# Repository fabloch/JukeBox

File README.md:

# Jukebox
Juke-Box avec une puce RFID

> Définition de Jukebox : Électrophone automatique, généralement payant, que l’on retrouve dans certains lieux publics et qui permet de faire jouer un disque sélectionné. (Définition d’Antidote)

> Définition de RFID : Sigle de Radio frequency identification.

Le Jukebox électriquement est composé de 3 parties : 
1. Une partie qui est en charge de la puce RFID 
2. La seconde partie quant à elle est chargée de la partie lecture du fichier MP3 et de l’amplification audio.
3. Le tout est supervisé par une carte Arduino UNO

## Liste des composant

- PUCE RFID
- Carte Arduino Uno 
- Boutons poussoir 
- Connecteur Jack 
- Amplificateur et lecteur de carte SD
- Potentiomètre 
	 
## Le code es quand à lui es écrit en Arduino 

Ici c’es le code de la partie du player du jukebox

```c
/*
   Thanks to Original Author: ryand1011 (https://github.com/ryand1011)
   Edited by Ananords -

   See: https://github.com/miguelbalboa/rfid/tree/master/examples/rfid_write_personal_data

   Uses MIFARE RFID card using RFID-RC522 reader
   Uses MFRC522 - Library
   -----------------------------------------------------------------------------------------
               MFRC522      Arduino       Arduino   Arduino    Arduino          Arduino
               Reader/PCD   Uno/101       Mega      Nano v3    Leonardo/Micro   Pro Micro
   Signal      Pin          Pin           Pin       Pin        Pin              Pin
   -----------------------------------------------------------------------------------------
   RST/Reset   RST          9             5         D9         RESET/ICSP-5     RST
   SPI SS      SDA(SS)      10            53        D10        10               10
   SPI MOSI    MOSI         11 / ICSP-4   51        D11        ICSP-4           16
   SPI MISO    MISO         12 / ICSP-1   50        D12        ICSP-1           14
   SPI SCK     SCK          13 / ICSP-3   52        D13        ICSP-3           15

  PS: IF THE PLAYER FAILS TO START WHEN THE SERIAL MONITOR IS NOT OPEN, TRY TO COMMENT OUT Serial.begin(115200);
*/

#include <SPI.h>
#include <MFRC522.h>
#include "Arduino.h"
#include "SoftwareSerial.h"
#include "DFRobotDFPlayerMini.h"

#define RST_PIN         9           // Configurable, see typical pin layout above
#define SS_PIN          10          // Configurable, see typical pin layout above

const int playPauseButton = 4;
const int shuffleButton = 3;
const byte volumePot = A0;
int prevVolume; 

byte volumeLevel = 0; //variable for holding volume level

boolean isPlaying = false;

MFRC522 mfrc522(SS_PIN, RST_PIN);   // Create MFRC522 instance

SoftwareSerial mySoftwareSerial(5, 6); // RX, TX

DFRobotDFPlayerMini myDFPlayer;
void printDetail(uint8_t type, int value);

//*****************************************************************************************//
void setup() {
  Serial.begin(115200);                                           // Initialize serial communications with the PC, COMMENT OUT IF IT FAILS TO PLAY WHEN DISCONNECTED FROM PC
  mySoftwareSerial.begin(9600);
  SPI.begin();                                                  // Init SPI bus
  mfrc522.PCD_Init();                                              // Init MFRC522 card

  pinMode(playPauseButton, INPUT_PULLUP);
  pinMode(shuffleButton, INPUT_PULLUP);

  Serial.println(F("Initializing DFPlayer ... (May take 3~5 seconds)"));

  if (!myDFPlayer.begin(mySoftwareSerial)) {  //Use softwareSerial to communicate with mp3.
    Serial.println(F("Unable to begin:"));
    Serial.println(F("1.Please recheck the connection!"));
    Serial.println(F("2.Please insert the SD card!"));
  }
  Serial.println(F("DFPlayer Mini online. Place card on reader to play a spesific song"));

  //myDFPlayer.volume(15);  //Set volume value. From 0 to 30 
  volumeLevel = map(analogRead(volumePot), 0, 1023, 0, 30);   //scale the pot value and volume level
  myDFPlayer.volume(volumeLevel);
  prevVolume = volumeLevel;

  //----Set different EQ----
  myDFPlayer.EQ(DFPLAYER_EQ_NORMAL);
  //  myDFPlayer.EQ(DFPLAYER_EQ_POP);
  //  myDFPlayer.EQ(DFPLAYER_EQ_ROCK);
  //  myDFPlayer.EQ(DFPLAYER_EQ_JAZZ);
  //  myDFPlayer.EQ(DFPLAYER_EQ_CLASSIC);
  //  myDFPlayer.EQ(DFPLAYER_EQ_BASS);

}

//*****************************************************************************************//
void loop() {

  volumeLevel = map(analogRead(volumePot), 0, 1023, 0, 30);   //scale the pot value and volume level

  if (prevVolume != volumeLevel){
  myDFPlayer.volume(volumeLevel);
  }
    prevVolume = volumeLevel;

  // Prepare key - all keys are set to FFFFFFFFFFFFh at chip delivery from the factory.
  MFRC522::MIFARE_Key key;
  for (byte i = 0; i < 6; i++) key.keyByte[i] = 0xFF;

  //some variables we need
  byte block;
  byte len;
  MFRC522::StatusCode status;

  if (digitalRead(playPauseButton) == LOW) {
    if (isPlaying) {
      myDFPlayer.pause();
      isPlaying = false;
      Serial.println("Paused..");
    }
    else {
      isPlaying = true;
      myDFPlayer.start();
      Serial.println("Playing..");
    }
    delay(500);
  }

  if (digitalRead(shuffleButton) == LOW) {
    myDFPlayer.randomAll();
    Serial.println("Shuffle Play");
    isPlaying = true;
    delay(1000);
  }

  //-------------------------------------------

  // Reset the loop if no new card present on the sensor/reader. This saves the entire process when idle.
  if ( mfrc522.PICC_IsNewCardPresent()) {

    // Select one of the cards
    if ( ! mfrc522.PICC_ReadCardSerial()) {
      return;
    }

    Serial.println(F("**Card Detected:**"));

    //-------------------------------------------

    mfrc522.PICC_DumpDetailsToSerial(&(mfrc522.uid)); //dump some details about the card

    //mfrc522.PICC_DumpToSerial(&(mfrc522.uid));      //uncomment this to see all blocks in hex

    //-------------------------------------------

    Serial.print(F("Number: "));

    //---------------------------------------- GET NUMBER AND PLAY THE SONG

    byte buffer2[18];
    block = 1;
    len = 18;

    status = mfrc522.PCD_Authenticate(MFRC522::PICC_CMD_MF_AUTH_KEY_A, 1, &key, &(mfrc522.uid)); //line 834
    if (status != MFRC522::STATUS_OK) {
      Serial.print(F("Authentication failed: "));
      Serial.println(mfrc522.GetStatusCodeName(status));
      return;
    }

    status = mfrc522.MIFARE_Read(block, buffer2, &len);
    if (status != MFRC522::STATUS_OK) {
      Serial.print(F("Reading failed: "));
      Serial.println(mfrc522.GetStatusCodeName(status));
      return;
    }

    //PRINT NUMBER
    String number = "";

    for (uint8_t i = 0; i < 16; i++)
    {
      number += (char)buffer2[i];
    }
    number.trim();
    Serial.print(number);

    //PLAY SONG

    myDFPlayer.play(number.toInt());
    isPlaying = true;

    //----------------------------------------

    Serial.println(F("\n**End Reading**\n"));

    delay(1000); //change value if you want to read cards faster

    mfrc522.PICC_HaltA();
    mfrc522.PCD_StopCrypto1();
  }
}

//*****************************************************************************************//

```

Juke Card programmer

Ici c’es le code source qui sert pour le programmer la jukebox. 

```c
/*
   Write song number data to a MIFARE RFID card using a RFID-RC522 reader
   Uses MFRC522 - Library to use ARDUINO RFID MODULE KIT 13.56 MHZ WITH TAGS SPI W AND R BY COOQROBOT.
   -----------------------------------------------------------------------------------------
               MFRC522      Arduino       Arduino   Arduino    Arduino          Arduino
               Reader/PCD   Uno/101       Mega      Nano v3    Leonardo/Micro   Pro Micro
   Signal      Pin          Pin           Pin       Pin        Pin              Pin
   -----------------------------------------------------------------------------------------
   RST/Reset   RST          9             5         D9         RESET/ICSP-5     RST
   SPI SS      SDA(SS)      10            53        D10        10               10
   SPI MOSI    MOSI         11 / ICSP-4   51        D11        ICSP-4           16
   SPI MISO    MISO         12 / ICSP-1   50        D12        ICSP-1           14
   SPI SCK     SCK          13 / ICSP-3   52        D13        ICSP-3           15

   Hardware required:
   Arduino
   PCD (Proximity Coupling Device): NXP MFRC522 Contactless Reader IC
   PICC (Proximity Integrated Circuit Card): A card or tag using the ISO 14443A interface, eg Mifare or NTAG203.
   The reader can be found on eBay for around 5 dollars. Search for "mf-rc522" on ebay.com or Aliexpress
*/

#include <SPI.h>
#include <MFRC522.h>

#define RST_PIN         9           // Configurable, see typical pin layout above
#define SS_PIN          10          // Configurable, see typical pin layout above

String mode;
int currentNumber = 1; //NUMBER TO START FROM

MFRC522 mfrc522(SS_PIN, RST_PIN);   // Create MFRC522 instance

void setup() {
  Serial.begin(115200);        // Initialize serial communications with the PC
  SPI.begin();               // Init SPI bus
  mfrc522.PCD_Init();        // Init MFRC522 card
  Serial.println(F("Write manual for Manual mode or auto for Automatic mode"));

}

void loop() {

  if (Serial.available()) {

    mode = Serial.readStringUntil('\n');

    if (mode == "auto" || "manual") {
      Serial.println(" ");
      Serial.println("Device is now in " + mode + " mode");
      Serial.println(F("Place the card on the reader and hold it there to write song number data to the card"));
      if (mode == "auto") Serial.println((String)"Number to be written to card: " + currentNumber);

    }

    while (mode == "auto") {

      autoModus();

    }

    while (mode == "manual") {

      manualModus();

    }

    if (mode != "auto" || "manual") {

      Serial.println("Wrong value, write auto or manual");

    }

  }

}

void autoModus() {

  // Prepare key - all keys are set to FFFFFFFFFFFFh at chip delivery from the factory.
  MFRC522::MIFARE_Key key;
  for (byte i = 0; i < 6; i++) key.keyByte[i] = 0xFF;

  // Reset the loop if no new card present on the sensor/reader. This saves the entire process when idle.
  if ( mfrc522.PICC_IsNewCardPresent()) {

    Serial.println(" ");

    // Select one of the cards
    if ( ! mfrc522.PICC_ReadCardSerial()) {
      return;
    }

    Serial.print(F("Card UID:"));    //Dump UID
    for (byte i = 0; i < mfrc522.uid.size; i++) {
      Serial.print(mfrc522.uid.uidByte[i] < 0x10 ? " 0" : " ");
      Serial.print(mfrc522.uid.uidByte[i], HEX);
    }

    Serial.print(F(" PICC type: "));   // Dump PICC type
    MFRC522::PICC_Type piccType = mfrc522.PICC_GetType(mfrc522.uid.sak);
    Serial.println(mfrc522.PICC_GetTypeName(piccType));

    byte buffer[16];
    MFRC522::StatusCode status;
    byte block;
    byte len;
    block = 1;

    len = sprintf(buffer, "%d", currentNumber);
    for (byte i = len; i < 30; i++) buffer[i] = ' ';

    //Serial.println(F("Authenticating using key A..."));
    status = mfrc522.PCD_Authenticate(MFRC522::PICC_CMD_MF_AUTH_KEY_A, block, &key, &(mfrc522.uid));
    if (status != MFRC522::STATUS_OK) {
      Serial.print(F("PCD_Authenticate() failed: "));
      Serial.println(mfrc522.GetStatusCodeName(status));
      return;
    }
    else Serial.println(F("PCD_Authenticate() success: "));

    // Write block
    status = mfrc522.MIFARE_Write(block, buffer, 16);
    if (status != MFRC522::STATUS_OK) {
      Serial.print(F("MIFARE_Write() failed: "));
      Serial.println(mfrc522.GetStatusCodeName(status));
      Serial.print(F("Try to reset the device"));
      return;
    }
    else Serial.println(F("MIFARE_Write() success: "));

    mfrc522.PICC_HaltA(); // Halt PICC
    mfrc522.PCD_StopCrypto1();  // Stop encryption on PCD

    currentNumber++;
    Serial.println((String)"Put a new card on the reader to write the number: " + currentNumber);

  }
}

void manualModus() {

  // Prepare key - all keys are set to FFFFFFFFFFFFh at chip delivery from the factory.
  MFRC522::MIFARE_Key key;
  for (byte i = 0; i < 6; i++) key.keyByte[i] = 0xFF;

  // Reset the loop if no new card present on the sensor/reader. This saves the entire process when idle.
  if ( ! mfrc522.PICC_IsNewCardPresent()) {
    return;
  }

  // Select one of the cards
  if ( ! mfrc522.PICC_ReadCardSerial()) {
    return;
  }

  Serial.print(F("Card UID:"));    //Dump UID
  for (byte i = 0; i < mfrc522.uid.size; i++) {
    Serial.print(mfrc522.uid.uidByte[i] < 0x10 ? " 0" : " ");
    Serial.print(mfrc522.uid.uidByte[i], HEX);
  }
  Serial.print(F(" PICC type: "));   // Dump PICC type
  MFRC522::PICC_Type piccType = mfrc522.PICC_GetType(mfrc522.uid.sak);
  Serial.println(mfrc522.PICC_GetTypeName(piccType));

  byte buffer[34];
  byte block;
  MFRC522::StatusCode status;
  byte len;

  Serial.setTimeout(20000L) ;     // wait until 20 seconds for input from serial
  // Ask for song number data
  Serial.println(F("Type any number and hit send/enter"));
  len = Serial.readBytesUntil('\n', (char *) buffer, 30) ; // read number from serial
  for (byte i = len; i < 30; i++) buffer[i] = ' ';     // pad with spaces

  block = 1;
  //Serial.println(F("Authenticating using key A..."));
  status = mfrc522.PCD_Authenticate(MFRC522::PICC_CMD_MF_AUTH_KEY_A, block, &key, &(mfrc522.uid));
  if (status != MFRC522::STATUS_OK) {
    Serial.print(F("PCD_Authenticate() failed: "));
    Serial.println(mfrc522.GetStatusCodeName(status));
    return;
  }
  else Serial.println(F("PCD_Authenticate() success: "));

  // Write block
  status = mfrc522.MIFARE_Write(block, buffer, 16);
  if (status != MFRC522::STATUS_OK) {
    Serial.print(F("MIFARE_Write() failed: "));
    Serial.println(mfrc522.GetStatusCodeName(status));
    return;
  }
  else Serial.println(F("MIFARE_Write() success: "));

  Serial.println("Put a new card on the reader to write a new number");

  Serial.println(" ");
  mfrc522.PICC_HaltA(); // Halt PICC
  mfrc522.PCD_StopCrypto1();  // Stop encryption on PCD

}

```

### Liens 

[https://fr.wikipedia.org/wiki/Arduino](https://fr.wikipedia.org/wiki/Arduino)
[https://github.com/miguelbalboa/rfid/tree/master/examples/rfid\_write\_personal\_data](https://github.com/miguelbalboa/rfid/tree/master/examples/rfid_write_personal_data)

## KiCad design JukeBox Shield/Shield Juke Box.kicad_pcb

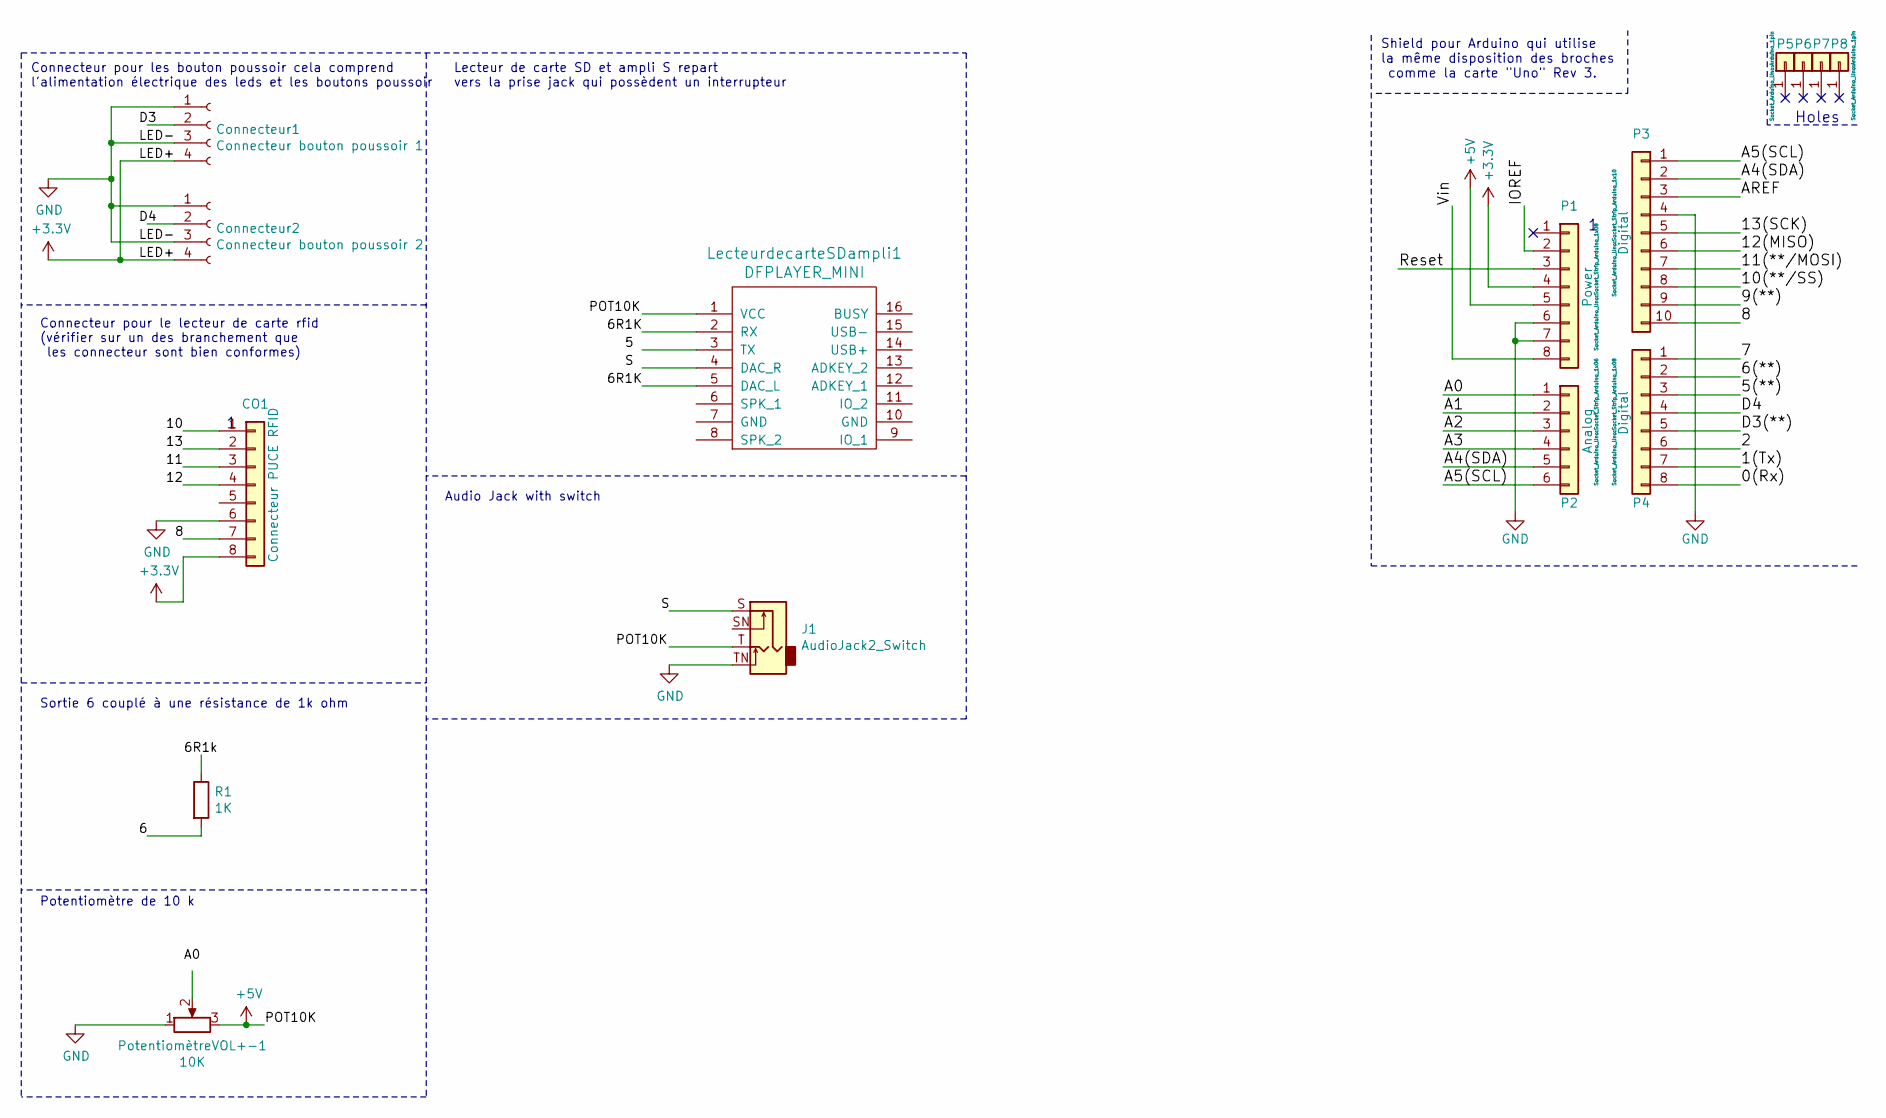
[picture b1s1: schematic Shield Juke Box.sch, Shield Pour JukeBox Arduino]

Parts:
CO1: Connecteur PUCE RFID; Socket_Strip_Arduino_1x08
Connecteur1: Connecteur bouton poussoir 1; Molex_CLIK-Mate_502382-0470_1x04-1MP_P1.25mm_Vertical
Connecteur2: Connecteur bouton poussoir 2; Molex_CLIK-Mate_502382-0470_1x04-1MP_P1.25mm_Vertical
J1: AudioJack2_Switch
LecteurdecarteSDampli1: DFPLAYER_MINI; Socket_Strip_Arduino_1x08
P1: Power; Socket_Strip_Arduino_1x08
P2: Analog; Socket_Strip_Arduino_1x06
P3: Digital; Socket_Strip_Arduino_1x10
P4: Digital; Socket_Strip_Arduino_1x08
P5, P6, P7, P8: CONN_01X01; Arduino_1pin
PotentiomètreVOL+-1: 10K; Molex_CLIK-Mate_502382-0370_1x03-1MP_P1.25mm_Vertical
R1: 1K; R_Axial_DIN0204_L3.6mm_D1.6mm_P1.90mm_Vertical

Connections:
+3V3: CO1.8, Connecteur1.4, Connecteur2.4, P1.4
+5V: P1.5, PotentiomètreVOL+-1.3
/0(Rx): P4.8
/1(Tx): P4.7
/2: P4.6
/5(**): LecteurdecarteSDampli1.3 (TX), P4.3
/6(**): P4.2
/7: P4.1
/8: P3.10
/9(**): P3.9
/10(**/SS): P3.8
/11(**/MOSI): P3.7
/12(MISO): P3.6
/13(SCK): P3.5
/A0: P2.1
/A1: P2.2
/A2: P2.3
/A3: P2.4
/A4(SDA): P2.5, P3.2
/A5(SCL): P2.6, P3.1
/AREF: P3.3
/D3(**): P4.5
/D4: P4.4
/IOREF: P1.2
/Reset: P1.3
/Vin: P1.8
GND: CO1.6, Connecteur1.1, Connecteur1.3, Connecteur2.1, Connecteur2.3, J1.TN, P1.6, P1.7, P3.4, PotentiomètreVOL+-1.1
unnamed: LecteurdecarteSDampli1.1 (VCC), PotentiomètreVOL+-1.2
unnamed: LecteurdecarteSDampli1.2 (RX), LecteurdecarteSDampli1.5 (DAC_L), R1.1

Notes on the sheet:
Holes
Shield pour Arduino qui utilise la même disposition des broches comme la carte "Uno" Rev 3.
Connecteur pour les bouton poussoir cela comprend l'alimentation électrique des leds et les boutons poussoir
Connecteur pour le lecteur de carte rfid (vérifier sur un des branchement que les connecteur sont bien conformes)
Sortie 6 couplé à une résistance de 1k ohm
Potentiomètre de 10 k
Lecteur de carte SD et ampli S repart vers la prise jack qui possèdent un interrupteur
Audio Jack with switch

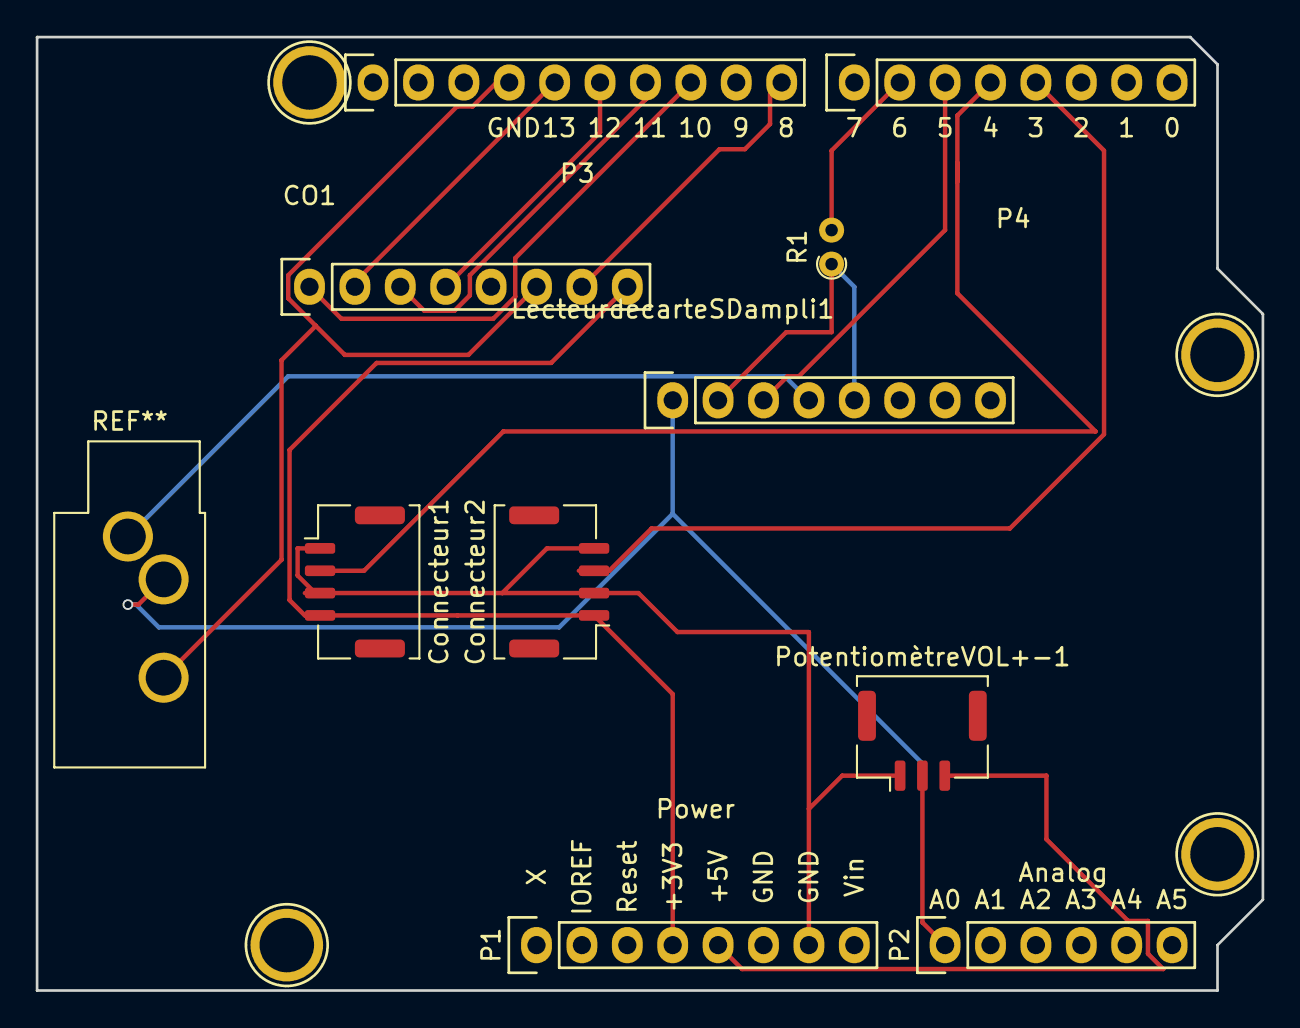
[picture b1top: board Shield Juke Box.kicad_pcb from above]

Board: 2 copper layers, 68.6 x 53.3 mm, 14 parts (0 on the bottom side), 8 nets.

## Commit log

2021-07-30 Create Schéma électrique JukeBox lisez moi
2021-07-30 Add files via upload
    Fichier du schéma électrique de la JukeBox crée sur Kicad version 5.1.10
2021-07-30 Rename Schéma électrique JukeBox lisez moi to Schéma électrique JukeBox lisez moi.md
2021-07-30 Create JukeBox Shield.md
    JukeBox shiel
2021-07-30 Add files via upload
    Fichier pour les PCB et le schéma électrique du Shield
2021-08-04 Update README.md
    Améliorer du fichier readme.md rajout de nouveau texte dans les fonctionnalité.
2021-08-04 Update README.md
    Version où les fautes d'orthographe on été révisé pour la plupart.
2021-08-04 Update Schéma électrique JukeBox lisez moi.md
    Orthographe révisé
2021-08-05 Add files via upload
    Fichier en .ino
